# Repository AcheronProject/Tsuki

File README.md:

# Acheron 60-SM-S-STM32-MX-TH-WI (Codename "Tsuki")

See [this page](https://gondolindrim.github.io/AcheronDocs/tsuki/intro.html) for the Tsuki documentation.

## Introduction

Tsuki is a universal 60% PCB, supporting per-key lighting using single-color LEDs, RGB underglow using WS2812C RGB LEDs and a multitude of layouts:

- Default ANSI bottom row;
- Classic HHKB (6.0u spacebar) bottom row;
- Tsangan bottom row (7.0u spacebar, also known as "simmetrical HHKB")
- Split backspace;
- Split left and right shifts;
- ISO and UK-ISO;
- ABNT and ABNT2 layouts.

Tsuki was heavily based on the [GH60](https://github.com/komar007/gh60), a legendary PCB designed by Komar with extensive feedback from the community.

## Contributors

- Raphael "ArcticFox" Hochheim for helping choosing the compatible layouts and the naming of the PCBs
- Felipe 'MrKeebs" Coury who paid for the V1 prototypes and helped immensely by funding my learning

## Renders

Click at the images to zoom in.

Renders generated by the [tracespace.io](https://tracespace.io/view/) site.

## Supported layouts

Click [this link](http://www.keyboard-layout-editor.com/#/gists/a08f081ffa5e553c9e5ae899616ba2f6) for the KLE file for the Tsuki.

## Copyright notice

This project is released under the Acheron Open-Hardware License V1.2. For the license, please refer to the LICENCE.md file.

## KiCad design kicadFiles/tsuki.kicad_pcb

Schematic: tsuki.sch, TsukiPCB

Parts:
CB1, CB3, CB7: 100n; C_0402_1005Metric
CB2: 100nF; C_0402_1005Metric
CB4, CB8: 4.7uF; C_0402_1005Metric
CB5: 1uF; C_0402_1005Metric
CB6: 10n; C_0402_1005Metric
CR1, CR2: 100n; C_0805_2012Metric
CR3: 4.7n; C_0805_2012Metric_Pad1.15x1.40mm_HandSolder
CR4: 10u; C_0805_2012Metric_Pad1.15x1.40mm_HandSolder
CRGB1, CRGB2, CRGB3, CRGB4, CRGB5, CRGB6, CRGB7, CRGB8, CRGB9, CRGB10: 100n; C_0805_2012Metric
CSH1, CSH2: 4.7nF; C_0805_2012Metric
CSI1: 1u; C_0805_2012Metric_Pad1.15x1.40mm_HandSolder
CSO1: 1u; C_0805_2012Metric_Pad1.15x1.40mm_HandSolder
D1, D2, D3, D4, D5, D6, D7, D8, D9, D10, D11, D12, D13, D14, D15, D16, D17, D18, D19, D20, D21, D22, D23, D24, D25, D26, D27, D28, D29, D30, D31, D32, D33, D34, D35, D36, D37, D38, D39, D40, D41, D42, D43, D44, D45, D46, D47, D48, D49, D50, D51, D52, D53, D54, D55, D56, D57, D58, D59, D60, D61, D62, D63, D64, D65: 1N4148; D_SOD-123
DF1: SMF9.0CA; D_SOD-123
DR1: 1N4148; D_SOD-123
DS1: RB060M-60TR; D_SOD-123
F1: 1.5A trip PTC; Fuse_1812_4532
H1, H6: Half Side Hole; halfSideHole
H2: Mounting Hole; MoutingHole_Oval_BackOnly_7mm_5.0x2.5mm
H3, H4, H5, H7, H9, H10: Oval Mounting Hole; MoutingHole_Oval_BackOnly_7mm_5.0x2.5mm
H8: Oval Mounting Hole; MoutingHole_Oval_7mm_5.0x2.5mm
J1: Conn_ARM_JTAG_SWD_10
J2: Conn_01x12; PinHeader_1x10_P2.54mm_Vertical
J3: TYPE-C-31-M12_13; TYPE-C-31-M-12
L1: OSHLogo; osh-logo
L2, L3, L5, L7: Warning; warning_sign_3.6x3.2mm
L4: Tsuki Logo; tsukiLogo_plated_25x11mm
L6: Acheron Logo; acheronLong
L8: TsukiLabel; tsukiLabel_30x12mm
L9: Tsuki Big Logo; tsukiLogo_90x115mm
LED1, LED2, LED3, LED4, LED5, LED6, LED7, LED8, LED9, LED10, LED11, LED12, LED13, LED14, LED15, LED16, LED17, LED18, LED19, LED20, LED21, LED22, LED23, LED24, LED25, LED26, LED27, LED28, LED29, LED30, LED31, LED32, LED33, LED34, LED35, LED36, LED37, LED38, LED39, LED40, LED41, LED42, LED43, LED44, LED45, LED46, LED47, LED48, LED49, LED50, LED51, LED52, LED53, LED54, LED55, LED56, LED57, LED58, LED59, LED60, LED61, LED62, LED63, LED64, LED65, LED66, LED67, LED68, LED69, LED70, LED71, LED72, LED73, LED74, LED75, LED76, LED77, LED78, LED79: LED; LED_THT_2.54mm
Q1: BSS138; SOT-23
QLED1: AO4407A; SOIC-8
QLED2: DTC123J; SOT-23
QRST1: DTC123J; SOT-23
RCC1, RCC2: 5.1k; R_SMD_1206
RGB1, RGB2, RGB3, RGB4, RGB5, RGB6, RGB7, RGB8, RGB9, RGB10: WS2812B; LED_WS2812B_5.0x5.0mm_P3.2mm
RGND1: R01; R_SMD_1206
RL1, RL2, RL3, RL4, RL5, RL6, RL7, RL8, RL9, RL10, RL11, RL12, RL13, RL14, RL15, RL16, RL17, RL18, RL19, RL20, RL21, RL22, RL23, RL24, RL25, RL26, RL27, RL28, RL29, RL30, RL31, RL32, RL33, RL34, RL35, RL36, RL37, RL38, RL39, RL40, RL41, RL42, RL43, RL44, RL45, RL46, RL47, RL48, RL49, RL50, RL51, RL52, RL53, RL54, RL55, RL56, RL57, RL58, RL59, RL60, RL61, RL62, RL63, RL64, RL65, RL66: 420R; R_SMD_1206
RLED1, RLED2: 10k; R_SMD_1206
RLED3: 100R; R_SMD_1206
ROT1: Rotary_Encoder_Switch; ALPS_EC11E
RR1, RR2, RR3, RR4: 10k; R_SMD_1206
RR5: 100k; R_SMD_1206
RRGB1, RRGB2, RRGB3, RRGB4, RRGB5, RRGB6, RRGB7, RRGB8, RRGB9, RRGB10: 5.1R; R_SMD_1206
RS1, RS2: 10k; R_SMD_1206
RSH1, RSH2: 1M; R_SMD_1206
RSI1: 100k; R_SMD_1206
RSO1: 100k; R_SMD_1206
SW1: 1U LBKSP; MX100
SW2: ESC; MX100
SW3: 1; MX100
SW4: 2; MX100
SW5: 3; MX100
SW6: 4; MX100
SW7: 5; MX100
SW8: 6; MX100
SW9: 7; MX100
SW10: 8; MX100
SW11: 9; MX100
SW12: 0; MX100
SW13: -_; MX100
SW14: +=; MX100
SW15: 2U BKSP; MX200
SW16: TAB_150; MX150
SW17: Q; MX100
SW18: W; MX100
SW19: E; MX100
SW20: R; MX100
SW21: T; MX100
SW22: Y; MX100
SW23: U; MX100
SW24: I; MX100
SW25: O; MX100
SW26: P; MX100
SW27: [{; MX100
SW28: ]}; MX100
SW29: 1U RBKSP; MX100
SW30: STEPPED_CAPS_125; MX125
SW31: CAPS_175; MX175
SW32: A; MX100
SW33: S; MX100
SW34: D; MX100
SW35: F; MX100
SW36: G; MX100
SW37: H; MX100
SW38: J; MX100
SW39: K; MX100
SW40: L; MX100
SW41: :;; MX100
SW42: \"'; MX100
SW43: \\|_150; MX150
SW44: ENTER_225; MX225
SW45: ISO_ENTER; MX_ISOEnter_Vertical_LED
SW46: RSHIFT_175; MX175
SW47: LSHIFT_225; MX225
SW48: ISO_100; MX100
SW49: Z; MX100
SW50: X; MX100
SW51: C; MX100
SW52: V; MX100
SW53: B; MX100
SW54: N; MX100
SW55: M; MX100
SW56: <,; MX100
SW57: >.; MX100
SW58: ?/; MX100
SW59: RSHIFT_275; MX275
SW60: ISO_\\_100; MX100
SW61: LSHIFT_125; MX125
SW62: LCTRL_150; MX150
SW63, SW77: RALT_150; MX150
SW64, SW78: RGUI_100; MX100
SW65: FN_100; MX100
SW66: LCTRL_125; MX125
SW67: LGUI_125; MX125
SW68: LALT_125; MX125
SW69: SPACE_625; MX625R
SW70: RALT_125; MX125
SW71: FN_125; MX125
SW72: RGUI_125; MX125
SW73: RCTRL_125; MX125
SW74: LGUI_100; MX100
SW75: LALT_150; MX150
SW76: SPACE_700; MX700R
SW79: RCTRL_150; MX150
SWR1: SW_Push; smdPushBtn
U1: USBLC6-2SC6; SOT-23-6
U2: STM32F072-LQFP48; LQFP-48_7x7mm_P0.5mm
U3: MCP1700-3302E_SOT23; SOT-23

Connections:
3.3V: CB1.2, CB2.1, CB3.2, CB4.2, CB5.2, CB6.2, CB7.2, CB8.2, CSO1.2, DS1.2 (A), J1.1 (VTref), Q1.1 (G), RR1.1, RR2.1, RS2.1, RSO1.1, SWR1.1, U2.1 (VBAT), U2.9 (VDDA), U2.24 (VDD), U2.36 (VDDIO2), U2.48 (VDD), U3.2 (VO)
5V: CSI1.2, DF1.1 (A1), DS1.1 (K), F1.1, QLED1.1 (S), QLED1.2 (S), QLED1.3 (S), RLED1.1, RLED2.2, RRGB1.1, RRGB2.1, RRGB3.1, RRGB4.1, RRGB5.1, RRGB6.1, RRGB7.1, RRGB8.1, RRGB9.1, RRGB10.1, RS1.1, RSI1.1, U3.3 (VI)
/SHIELD: CSH2.2, J3.S (SHIELD), RSH2.1
BOOT0: CR4.2, DR1.1 (K), RR5.1, U2.44 (BOOT0)
CASE: CSH1.2, H8.1, RSH1.1
Col1: SW2.1 (Col), SW16.1 (Col), SW30.2 (Row), SW31.1 (Col), SW47.1 (Col), SW61.1 (Col), SW62.1 (Col), SW66.1 (Col), U2.25 (PB12)
Col2: SW3.1 (Col), SW17.1 (Col), SW32.1 (Col), SW48.1 (Col), SW67.1 (Col), SW74.1 (Col), U2.12 (PA2/ADC_IN2)
Col3: SW4.1 (Col), SW18.1 (Col), SW33.1 (Col), SW49.1 (Col), SW68.1 (Col), SW75.1 (Col), U2.11 (PA1/ADC_IN1)
Col4: SW5.1 (Col), SW19.1 (Col), SW34.1 (Col), SW50.1 (Col), U2.10 (PA0/ADC_IN0)
Col5: SW6.1 (Col), SW20.1 (Col), SW35.1 (Col), SW51.1 (Col), U2.6 (PF1/OSC_OUT)
Col6: SW7.1 (Col), SW21.1 (Col), SW36.1 (Col), SW52.1 (Col), U2.5 (PF0/OSC_IN)
Col7: SW8.1 (Col), SW22.1 (Col), SW37.1 (Col), SW53.1 (Col), SW69.1 (Col), SW76.1 (Col), U2.4 (PC15/OSC32_OUT)
Col8: SW9.1 (Col), SW23.1 (Col), SW38.1 (Col), SW54.1 (Col), U2.3 (PC14/OSC32_IN)
Col9: SW10.1 (Col), SW24.1 (Col), SW39.1 (Col), SW55.1 (Col), U2.20 (PB2)
Col10: SW11.1 (Col), SW25.1 (Col), SW40.1 (Col), SW56.1 (Col), SW63.1 (Col), SW70.1 (Col), U2.19 (PB1/TIM3_CH4/TIM14_CH1/ADC_IN9)
Col11: SW12.1 (Col), SW26.1 (Col), SW41.1 (Col), SW57.1 (Col), SW64.1 (Col), SW71.1 (Col), SW77.1 (Col), U2.18 (PB0/TIM3_CH3/ADC_IN8)
Col12: SW13.1 (Col), SW27.1 (Col), SW42.1 (Col), SW58.1 (Col), SW72.1 (Col), SW78.1 (Col), U2.17 (PA7/TIM3_CH2/TIM14_CH1/ADC_IN7)
Col13: SW14.1 (Col), SW28.1 (Col), SW43.1 (Col), SW46.1 (Col), SW59.1 (Col), SW73.1 (Col), SW79.1 (Col), U2.15 (PA5/ADC_IN5/DAC_OUT2)
Col14: ROT1.S2, SW1.1 (Col), SW15.1 (Col), SW29.1 (Col), SW44.1 (Col), SW45.1 (Col), SW60.1 (Col), SW65.1 (Col), U2.14 (PA4/TIM14_CH1/ADC_IN4)
D+: U1.3 (IO2), U2.33 (USB_DP/PA12)
D-: U1.1 (IO1), U2.32 (USB_DM/TIM1_CH4/PA11)
DBus+: J3.A7 (D-), J3.B7 (D-), U1.4 (IO2)
DBus-: J3.A6 (D+), J3.B6 (D+), U1.6 (IO1)
ENC_A: CR2.1, RR4.2, U2.46 (SPI2_NSS/I2S2_WS/I2C1_SDA/TIM17_CH1/PB9)
ENC_B: CR1.1, RR3.2, U2.2 (PC13)
Extra3: J2.1, U2.42 (I2C1_SCL/PB6)
Extra4: J2.2, U2.41 (SPI1_MOSI/I2S1_SD/TIM3_CH2/PB5)
Extra5: J2.3, U2.40 (SPI1_MISO/I2S1_MCK/TIM3_CH1/PB4)
Extra6: J2.4, U2.39 (SPI1_SCK/I2S1_CK/TIM2_CH2/PB3)
Extra7: J2.5, U2.38 (PA2)
Extra8: J2.6, U2.31 (TIM1_CH3/PA10)
Extra9: J2.7, U2.30 (TIM1_CH2/PA9)
Extra10: J2.8, U2.29 (TIM1_CH1/PA8)
Extra11: J2.9, U2.27 (PB14/SPI2_MISO/I2S2_MCK/I2C2_SDA/TIM15_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)
Extra12: J2.10, U2.26 (SPI2_SCK/I2S2_CK/I2C2_SCL/PB13)
GND: CR1.2, CR2.2, CR3.2, CR4.1, CRGB1.2, CRGB2.2, CRGB3.2, CRGB4.2, CRGB5.2, CRGB6.2, CRGB7.2, CRGB8.2, CRGB9.2, CRGB10.2, CSH1.1, CSH2.1, CSI1.1, CSO1.1, DF1.2 (A2), J1.3 (GND), J1.5 (GND), J1.9 (GNDDetect), J3.A1 (GND), J3.B1 (GND), LED1.K, LED2.K, LED3.K, LED4.K, LED5.K, LED6.K, LED7.K, LED8.K, LED9.K, LED10.K, LED11.K, LED12.K, LED13.K, LED14.K, LED15.K, LED16.K, LED17.K, LED18.K, LED19.K, LED20.K, LED21.K, LED22.K, LED23.K, LED24.K, LED25.K, LED26.K, LED27.K, LED28.K, LED29.K, LED30.K, LED31.K, LED32.K, LED33.K, LED34.K, LED35.K, LED36.K, LED37.K, LED38.K, LED39.K, LED40.K, LED41.K, LED42.K, LED43.K, LED44.K, LED45.K, LED46.K, LED47.K, LED48.K, LED49.K, LED50.K, LED51.K, LED52.K, LED53.K, LED54.K, LED55.K, LED56.K, LED57.K, LED58.K, LED59.K, LED60.K, LED61.K, LED62.K, LED63.K, LED64.K, LED65.K, LED66.K, LED67.K, LED68.K, LED69.K, LED70.K, LED71.K, LED72.K, LED73.K, LED74.K, LED75.K, LED76.K, LED77.K, LED78.K, LED79.K, QLED2.2 (E), QRST1.2 (E), RCC1.1, RCC2.1, RGB1.3 (VSS), RGB2.3 (VSS), RGB3.3 (VSS), RGB4.3 (VSS), RGB5.3 (VSS), RGB6.3 (VSS), RGB7.3 (VSS), RGB8.3 (VSS), RGB9.3 (VSS), RGB10.3 (VSS), RGND1.2, ROT1.C, RR5.2, RSH1.2, RSH2.2, RSI1.2, RSO1.2, U1.2 (GND), U3.1 (GND)
GNDD: CB1.1, CB2.2, CB3.1, CB4.1, CB5.1, CB6.1, CB7.1, CB8.1, RGND1.1, U2.8 (VSSA), U2.23 (VSS), U2.35 (VSS), U2.47 (VSS)
L1: D57.2 (A), SW62.2 (Row), SW66.2 (Row)
L2: D63.2 (A), SW67.2 (Row), SW74.2 (Row)
L3: D64.2 (A), SW68.2 (Row), SW75.2 (Row)
L5: D58.2 (A), SW69.2 (Row), SW76.2 (Row)
L6: D59.2 (A), SW63.2 (Row), SW70.2 (Row)
L7: D60.2 (A), SW64.2 (Row), SW71.2 (Row), SW77.2 (Row)
L8: D62.2 (A), SW72.2 (Row), SW78.2 (Row)
L9: D65.2 (A), SW73.2 (Row), SW79.2 (Row)
LED_PWM: QLED2.1 (B), U2.16 (PA6/ADC_IN6/TIM3_CH1/TIM16_CH1)
NRST: CR3.1, J1.10 (~RESET~), QRST1.3 (C), U2.7 (NRST)
unnamed: CRGB1.1, RGB1.1 (VDD), RRGB1.2
unnamed: CRGB2.1, RGB2.1 (VDD), RRGB2.2
unnamed: CRGB3.1, RGB3.1 (VDD), RRGB3.2
unnamed: CRGB4.1, RGB4.1 (VDD), RRGB4.2
unnamed: CRGB5.1, RGB5.1 (VDD), RRGB5.2
unnamed: CRGB6.1, RGB6.1 (VDD), RRGB6.2
unnamed: CRGB7.1, RGB7.1 (VDD), RRGB7.2
unnamed: CRGB8.1, RGB8.1 (VDD), RRGB8.2
unnamed: CRGB9.1, RGB9.1 (VDD), RRGB9.2
unnamed: CRGB10.1, RGB10.1 (VDD), RRGB10.2
unnamed: D1.2 (A), SW2.2 (Row)
unnamed: D2.2 (A), SW3.2 (Row)
unnamed: D3.2 (A), SW4.2 (Row)
unnamed: D4.2 (A), SW5.2 (Row)
unnamed: D5.2 (A), SW6.2 (Row)
unnamed: D6.2 (A), SW7.2 (Row)
unnamed: D7.2 (A), SW8.2 (Row)
unnamed: D8.2 (A), SW9.2 (Row)
unnamed: D9.2 (A), SW10.2 (Row)
unnamed: D10.2 (A), SW11.2 (Row)
unnamed: D11.2 (A), SW12.2 (Row)
unnamed: D12.2 (A), SW13.2 (Row)
unnamed: D13.2 (A), SW14.2 (Row)
unnamed: D14.2 (A), SW1.2 (Row), SW15.2 (Row)
unnamed: D15.2 (A), SW16.2 (Row)
unnamed: D16.2 (A), SW17.2 (Row)
unnamed: D17.2 (A), SW18.2 (Row)
unnamed: D18.2 (A), SW19.2 (Row)
unnamed: D19.2 (A), SW20.2 (Row)
unnamed: D20.2 (A), SW21.2 (Row)
unnamed: D21.2 (A), SW22.2 (Row)
unnamed: D22.2 (A), SW23.2 (Row)
unnamed: D23.2 (A), SW24.2 (Row)
unnamed: D24.2 (A), SW25.2 (Row)
unnamed: D25.2 (A), SW26.2 (Row)
unnamed: D26.2 (A), SW27.2 (Row)
unnamed: D27.2 (A), SW28.2 (Row)
unnamed: D28.2 (A), SW29.2 (Row)
unnamed: D29.2 (A), SW30.1 (Col), SW31.2 (Row)
unnamed: D30.2 (A), SW32.2 (Row)
unnamed: D31.2 (A), SW33.2 (Row)
unnamed: D32.2 (A), SW34.2 (Row)
unnamed: D33.2 (A), SW35.2 (Row)
unnamed: D34.2 (A), SW36.2 (Row)
unnamed: D35.2 (A), SW37.2 (Row)
unnamed: D36.2 (A), SW38.2 (Row)
unnamed: D37.2 (A), SW39.2 (Row)
unnamed: D38.2 (A), SW40.2 (Row)
unnamed: D39.2 (A), SW41.2 (Row)
unnamed: D40.2 (A), SW42.2 (Row)
unnamed: D41.2 (A), SW43.2 (Row)
unnamed: D42.2 (A), SW44.2 (Row), SW45.2 (Row)
unnamed: D43.2 (A), SW47.2 (Row), SW61.2 (Row)
unnamed: D44.2 (A), SW48.2 (Row)
unnamed: D45.2 (A), SW49.2 (Row)
unnamed: D46.2 (A), SW50.2 (Row)
unnamed: D47.2 (A), SW51.2 (Row)
unnamed: D48.2 (A), SW52.2 (Row)
unnamed: D49.2 (A), SW53.2 (Row)
unnamed: D50.2 (A), SW54.2 (Row)
unnamed: D51.2 (A), SW55.2 (Row)
unnamed: D52.2 (A), SW56.2 (Row)
unnamed: D53.2 (A), SW57.2 (Row)
unnamed: D54.2 (A), SW58.2 (Row)
unnamed: D55.2 (A), SW46.2 (Row), SW59.2 (Row)
unnamed: D56.2 (A), SW60.2 (Row)
unnamed: DR1.2 (A), QRST1.1 (B), SWR1.2
unnamed: J3.A5 (CC1), RCC1.2
unnamed: J3.B5 (CC2), RCC2.2
unnamed: LED1.A, RL1.1
unnamed: LED2.A, RL2.1
unnamed: LED3.A, RL3.1
unnamed: LED4.A, RL4.1
unnamed: LED5.A, RL5.1
unnamed: LED6.A, RL6.1
unnamed: LED7.A, RL7.1
unnamed: LED8.A, RL8.1
unnamed: LED9.A, RL9.1
unnamed: LED10.A, RL10.1
unnamed: LED11.A, RL11.1
unnamed: LED12.A, RL12.1
unnamed: LED13.A, RL13.1
unnamed: LED14.A, LED15.A, RL14.1
unnamed: LED16.A, RL15.1
unnamed: LED17.A, RL16.1
unnamed: LED18.A, RL17.1
unnamed: LED19.A, RL18.1
unnamed: LED20.A, RL19.1
unnamed: LED21.A, RL20.1
unnamed: LED22.A, RL21.1
unnamed: LED23.A, RL22.1
unnamed: LED24.A, RL23.1
unnamed: LED25.A, RL24.1
unnamed: LED26.A, RL25.1
unnamed: LED27.A, RL26.1
unnamed: LED28.A, RL27.1
unnamed: LED29.A, RL28.1
unnamed: LED30.A, RL29.1
unnamed: LED31.A, LED32.A, RL30.1
unnamed: LED33.A, RL31.1
unnamed: LED34.A, RL32.1
unnamed: LED35.A, RL33.1
unnamed: LED36.A, RL34.1
unnamed: LED37.A, RL35.1
unnamed: LED38.A, RL36.1
unnamed: LED39.A, RL37.1
unnamed: LED40.A, RL38.1
unnamed: LED41.A, RL39.1
unnamed: LED42.A, RL40.1
unnamed: LED43.A, RL41.1
unnamed: LED44.A, RL42.1
unnamed: LED45.A, RL43.1
unnamed: LED46.A, RL44.1
unnamed: LED47.A, LED48.A, RL45.1
unnamed: LED49.A, RL46.1
unnamed: LED50.A, RL47.1
unnamed: LED51.A, RL48.1
unnamed: LED52.A, RL49.1
unnamed: LED53.A, RL50.1
unnamed: LED54.A, RL51.1
unnamed: LED55.A, RL52.1
unnamed: LED56.A, RL53.1
unnamed: LED57.A, RL54.1
unnamed: LED58.A, RL55.1
unnamed: LED59.A, RL56.1
unnamed: LED60.A, RL57.1
unnamed: LED61.A, LED62.A, RL58.1
unnamed: LED63.A, LED64.A, RL59.1
unnamed: LED65.A, LED66.A, RL60.1
unnamed: LED67.A, LED68.A, RL61.1
unnamed: LED69.A, LED70.A, RL62.1
unnamed: LED71.A, LED72.A, RL63.1
unnamed: LED73.A, LED74.A, LED75.A, RL64.1
unnamed: LED76.A, LED77.A, RL65.1
unnamed: LED78.A, LED79.A, RL66.1
unnamed: QLED1.4 (G), RLED2.1, RLED3.1
unnamed: QLED1.5 (D), QLED1.6 (D), QLED1.7 (D), QLED1.8 (D), RL1.2, RL2.2, RL3.2, RL4.2, RL5.2, RL6.2, RL7.2, RL8.2, RL9.2, RL10.2, RL11.2, RL12.2, RL13.2, RL14.2, RL15.2, RL16.2, RL17.2, RL18.2, RL19.2, RL20.2, RL21.2, RL22.2, RL23.2, RL24.2, RL25.2, RL26.2, RL27.2, RL28.2, RL29.2, RL30.2, RL31.2, RL32.2, RL33.2, RL34.2, RL35.2, RL36.2, RL37.2, RL38.2, RL39.2, RL40.2, RL41.2, RL42.2, RL43.2, RL44.2, RL45.2, RL46.2, RL47.2, RL48.2, RL49.2, RL50.2, RL51.2, RL52.2, RL53.2, RL54.2, RL55.2, RL56.2, RL57.2, RL58.2, RL59.2, RL60.2, RL61.2, RL62.2, RL63.2, RL64.2, RL65.2, RL66.2
unnamed: QLED2.3 (C), RLED1.2, RLED3.2
unnamed: RGB1.2 (DOUT), RGB2.4 (DIN)
unnamed: RGB2.2 (DOUT), RGB3.4 (DIN)
unnamed: RGB3.2 (DOUT), RGB4.4 (DIN)
unnamed: RGB4.2 (DOUT), RGB5.4 (DIN)
unnamed: RGB5.2 (DOUT), RGB6.4 (DIN)
unnamed: RGB6.2 (DOUT), RGB7.4 (DIN)
unnamed: RGB7.2 (DOUT), RGB8.4 (DIN)
unnamed: RGB8.2 (DOUT), RGB9.4 (DIN)
unnamed: RGB9.2 (DOUT), RGB10.4 (DIN)
RGB_3V3: Q1.2 (S), RS2.2, U2.28 (SPI2_MOSI/I2S2_SD/PB15)
RGB_5V: Q1.3 (D), RGB1.4 (DIN), RS1.2
ROT_A: ROT1.A, RR2.2, RR4.1
ROT_B: ROT1.B, RR1.2, RR3.1
ROT_S1: D61.2 (A), ROT1.S1, SW65.2 (Row)
Row1: D1.1 (K), D2.1 (K), D3.1 (K), D4.1 (K), D5.1 (K), D6.1 (K), D7.1 (K), D8.1 (K), D9.1 (K), D10.1 (K), D11.1 (K), D12.1 (K), D13.1 (K), D14.1 (K), U2.45 (I2C1_SCL/TIM16_CH1/PB8)
Row2: D15.1 (K), D16.1 (K), D17.1 (K), D18.1 (K), D19.1 (K), D20.1 (K), D21.1 (K), D22.1 (K), D23.1 (K), D24.1 (K), D25.1 (K), D26.1 (K), D27.1 (K), D28.1 (K), U2.43 (2C1_SDA/PB7)
Row3: D29.1 (K), D30.1 (K), D31.1 (K), D32.1 (K), D33.1 (K), D34.1 (K), D35.1 (K), D36.1 (K), D37.1 (K), D38.1 (K), D39.1 (K), D40.1 (K), D41.1 (K), D42.1 (K), U2.13 (PA3/TIM15_CH2/ADC_IN3)
Row4: D43.1 (K), D44.1 (K), D45.1 (K), D46.1 (K), D47.1 (K), D48.1 (K), D49.1 (K), D50.1 (K), D51.1 (K), D52.1 (K), D53.1 (K), D54.1 (K), D55.1 (K), D56.1 (K), U2.21 (PB10/SPI2_SCK/I2C2_SCL/TIM2_CH3)
Row5: D57.1 (K), D58.1 (K), D59.1 (K), D60.1 (K), D61.1 (K), D62.1 (K), D63.1 (K), D64.1 (K), D65.1 (K), U2.22 (PB11/TIM2_CH4/I2C2_SDA)
SWCLK: J1.4 (SWDCLK/TCK), U2.37 (SWCLK/PA14)
SWDIO: J1.2 (SWDIO/TMS), U2.34 (SWDIO/PA13)
VBUS: F1.2, J3.A4 (VBUS), J3.B4 (VBUS), U1.5 (VBUS)

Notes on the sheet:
Hard reset circuit
Power supply and protection circuit
Logos and flags
Serial programming
[1] STM32F072x8 / STM32F072xB datasheet
REFERENCES
https://www.st.com/resource/en/datasheet/stm32f072rb.pdf
[2] AN4080 Application note
https://www.st.com/content/ccc/resource/technical/document/application_note/c9/19/d7/b8/6b/0e/4c/d3/DM00051986.pdf/files/DM00051986.pdf/jcr:content/translations/en.DM00051986.pdf
MCU
USB Connector
Shield
USD ESD
CBx are the bypass capacitors. Their value is specified in reference [2].
Case ESD
Mounting holes
Extra pins
Observation: the 6U spacebar footprint is already covered by the 6.25+7U spacebar footprints
7U Bottom (T for Tsangan bottom)
6.25U Bottom (D for default ANSI)
6U Bottom (H for HHKB)
Switch matrix
RGB Underglow
Per-keys LEDs
Encoder
Warning signs

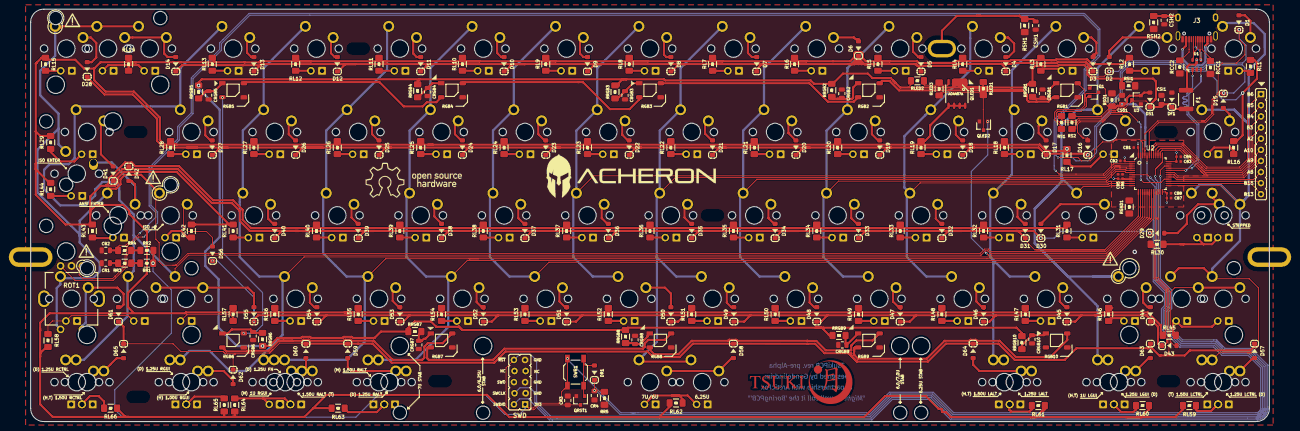
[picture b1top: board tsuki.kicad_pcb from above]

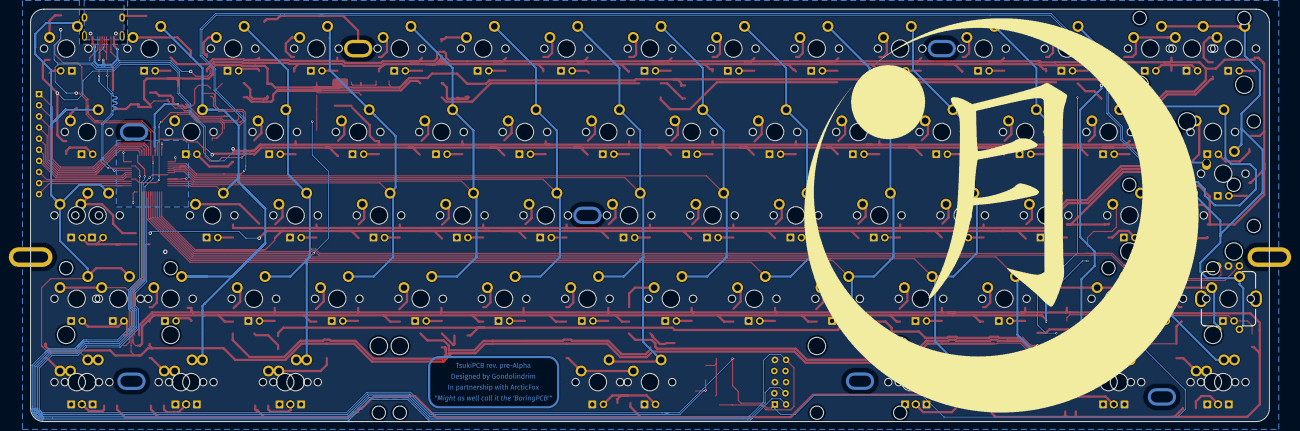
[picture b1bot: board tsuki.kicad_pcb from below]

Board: 2 copper layers, 283.0 x 94.2 mm, 387 parts (11 on the bottom side), 207 nets.

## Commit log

2019-12-12 Removed split space options
2019-12-12 Updated AcheronLibrary module
2019-12-13 Remove layouts, update li, add label, maintenance
    - The split backspace layouts were removed. This decision was made because I reckoned a very small amount of people would use them, and the PCB is already very compromised material-wise as it is.
    - The Acheron Library was updated, following the updates in other projects
    - A label was added signalling the pre-Revision Alpha
    - The footprints for the holes were all changed for the no-backside version, to avoid any unintended short-circuits
    - Indicative documentation and arrows were added for the bottom row layouts to facilitate building the PCB
2019-12-13 Added clearances to stab holes
2019-12-15 Added Schottky diodes and TVS
2019-12-15 Added discharge resistors RSI and RSO
2019-12-15 Added RGB to schematic
2019-12-15 Added LED control to schematic
2019-12-15 Added bottom row documentation
2019-12-18 Routed second row LEDs
2019-12-18 Finished routing
2020-01-03 Assign col and row pins
2020-01-04 Run DRC, finish pin assignment
2020-01-04 Add rotary encoder support
2020-01-04 Refreshed renders and KLE
2020-01-04 Adjusted schematic
2020-01-04 Further adjust schematic
2020-01-04 Refresh KLE, finish PCB and schematic
2020-01-04 Final preparations for release pre-Alpha
2020-01-04 Add initial Blender render
2020-02-03 Edit README
    Changed wording for clarification. (Otherwise, if not accepted, fix typo from `funcing` to `funding`.
